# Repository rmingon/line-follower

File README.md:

## Line follower

# Line Follower Robot - ATmega2560 Based

This project is a Line Follower Robot using an ATmega2560 microcontroller. It features motor control, a reflective sensor array for line tracking, a fan controller, and voltage regulation.

### 3D views

## Features

- MCU: ATmega2560-16A
- 10x QRE1113GR reflective IR sensors
- 2x MX1508 motor drivers (H-bridge)
- MOSFET-based fan control (2N7002)
- Power via battery with 5V regulation (AMS1117)
- 6x status LEDs
- Standard AVR ISP programming header
- Custom-designed PCB

## Hardware Overview

- Sensors connect to MCU ADC pins
- Motor drivers controlled via PWM
- Fan controlled via GPIO and MOSFET
- 16 MHz crystal oscillator with 22pF caps
- Power from battery regulated to 5V

## Components

| Component      | Part             | Description                    |
|----------------|------------------|--------------------------------|
| Microcontroller| ATmega2560-16A   | Main processing unit           |
| Motor Driver   | MX1508           | H-bridge for motor control     |
| Sensor         | QRE1113GR        | IR reflective sensor           |
| Regulator      | AMS1117-5.0      | 5V linear regulator            |
| MOSFET         | 2N7002           | Fan switching control          |
| Oscillator     | 16 MHz + 22pF    | Clock for MCU                  |
| LED            | Generic Red LED  | Status indicators              |
| Fan            | 5V Fan           | Pin to floor                   |

## Key MCU Pin Mapping

| Feature         | Pin (ATmega2560) |
|----------------|------------------|
| Motor A Control| PE4, PE5         |
| Motor B Control| PG5, PL7         |
| IR Sensors     | PF0–PF9          |
| Fan Control    | PD7              |
| LEDs           | PA0–PA5          |

## PCB Layout

Two zones:
1. Sensor array in a linear top arrangement for line detection.
2. Bottom section contains MCU, drivers, power, and headers.

## Usage Steps

1. Connect a battery to `+BATT` input.
2. Upload firmware using AVR ISP (J5).
3. Place on track with visible black line.
4. Adjust PID tuning in firmware for better tracking.

## Development Tools

- KiCad for circuit & PCB design
- AVR-GCC or PlatformIO for firmware
- AVRDude for programming

## File Structure

```
/hardware
  schematic.jpeg
  pcb.png
/firmware
  main.c / main.cpp
  Makefile / platformio.ini
README.md
```

## Author

Created by Rmingon - Robotics Developer

### PCB

### SCHEMATIC

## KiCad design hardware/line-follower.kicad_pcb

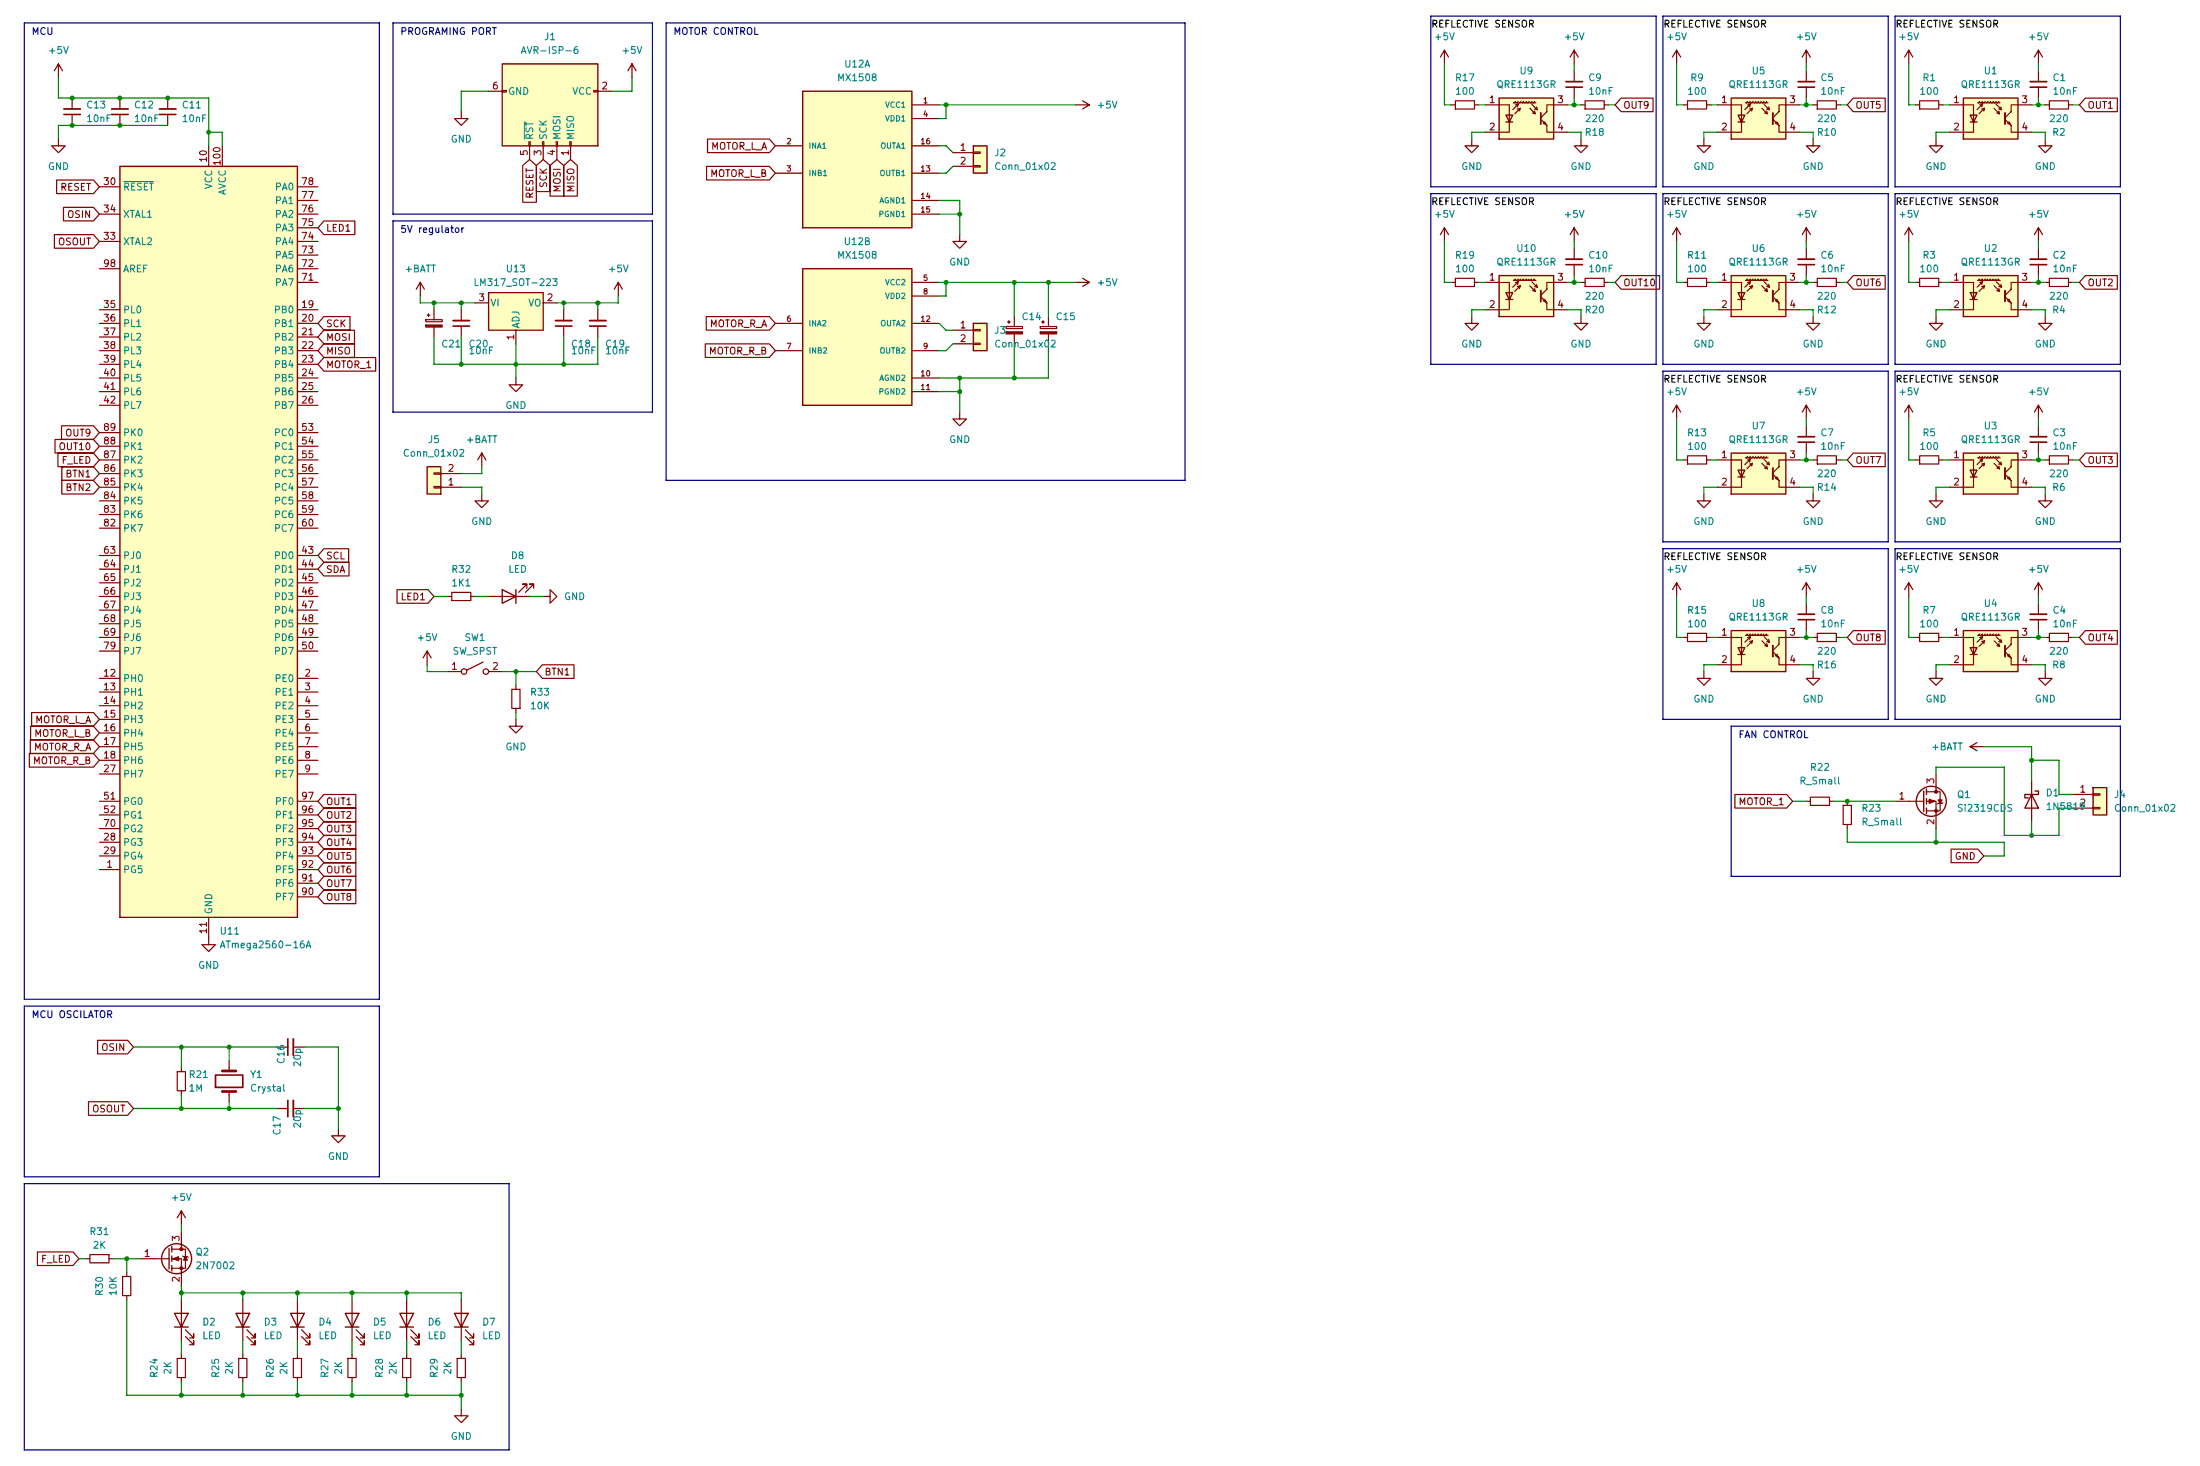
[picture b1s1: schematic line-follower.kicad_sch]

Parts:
C1, C2, C3, C4, C5, C6, C7, C8, C9, C10, C11, C12, C13, C18, C19, C20: 10nF; C_0603_1608Metric
C14, C15, C21: C_Polarized_Small; CP_Elec_6.3x4.9
C16, C17: 20p; C_0603_1608Metric
D1: 1N5819; D_DO-41_SOD81_P10.16mm_Horizontal
D2, D3, D4, D5, D6, D7, D8: LED; LED_0603_1608Metric
J1: AVR-ISP-6; PinHeader_2x03_P2.54mm_Vertical
J2, J3: Conn_01x02; PinSocket_1x02_P2.54mm_Vertical
J4: Conn_01x02; PinHeader_1x02_P2.54mm_Vertical
J5: Conn_01x02; TE_826576-2_1x02_P3.96mm_Vertical
Q1: Si2319CDS; SOT-23
Q2: 2N7002; SOT-23
R1, R3, R5, R7, R9, R11, R13, R15, R17, R19: 100; R_0603_1608Metric
R2, R4, R6, R8, R10, R12, R14, R16, R18, R20: 220; R_0603_1608Metric
R21: 1M; R_0603_1608Metric
R22, R23: R_Small; R_0603_1608Metric
R24, R25, R26, R27, R28, R29, R31: 2K; R_0603_1608Metric
R30, R33: 10K; R_0603_1608Metric
R32: 1K1; R_0603_1608Metric
SW1: SW_SPST; SW_SPST_FSMSM
U1, U2, U3, U4, U5, U6, U7, U8, U9, U10: QRE1113GR; OnSemi_CASE100CY
U11: ATmega2560-16A; TQFP-100_14x14mm_P0.5mm
U12: MX1508; SOIC-16W_5.3x10.2mm_P1.27mm
U13: LM317_SOT-223; SOT-223-3_TabPin2
Y1: Crystal; Crystal_SMD_HC49-SD

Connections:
+5V: C1.2, C2.2, C3.2, C4.2, C5.2, C6.2, C7.2, C8.2, C9.2, C10.2, C11.2, C12.2, C13.2, C14.1, C15.1, C18.2, C19.2, J1.2 (VCC), Q2.3 (D), R1.1, R3.1, R5.1, R7.1, R9.1, R11.1, R13.1, R15.1, R17.1, R19.1, SW1.1 (A), U11.10 (VCC), U11.31 (VCC), U11.61 (VCC), U11.80 (VCC), U11.100 (AVCC), U12.1 (VCC1), U12.4 (VDD1), U12.5 (VCC2), U12.8 (VDD2), U13.2 (VO)
+BATT: C20.2, C21.1, D1.1 (K), J4.1, J5.2, U13.3 (VI)
BTN1: R33.2, SW1.2 (B), U11.86 (PK3)
BTN2: U11.85 (PK4)
F_LED: R31.2, U11.87 (PK2)
GND: C11.1, C12.1, C13.1, C14.2, C15.2, C16.2, C17.2, C18.1, C19.1, C20.1, C21.2, D8.1 (K), J1.6 (GND), J5.1, Q1.2 (S), R23.2, R24.2, R25.2, R26.2, R27.2, R28.2, R29.2, R30.2, R33.1, U1.2 (K), U1.4, U2.2 (K), U2.4, U3.2 (K), U3.4, U4.2 (K), U4.4, U5.2 (K), U5.4, U6.2 (K), U6.4, U7.2 (K), U7.4, U8.2 (K), U8.4, U9.2 (K), U9.4, U10.2 (K), U10.4, U11.11 (GND), U11.32 (GND), U11.62 (GND), U11.81 (GND), U11.99 (GND), U12.10 (AGND2), U12.11 (PGND2), U12.14 (AGND1), U12.15 (PGND1), U13.1 (ADJ)
LED1: R32.1, U11.75 (PA3)
MISO: J1.1 (MISO), U11.22 (PB3)
MOSI: J1.4 (MOSI), U11.21 (PB2)
MOTOR_1: R22.1, U11.23 (PB4)
MOTOR_L_A: U11.15 (PH3), U12.2 (INA1)
MOTOR_L_B: U11.16 (PH4), U12.3 (INB1)
MOTOR_R_A: U11.17 (PH5), U12.6 (INA2)
MOTOR_R_B: U11.18 (PH6), U12.7 (INB2)
unnamed: C1.1, R2.1, U1.3
unnamed: C2.1, R4.1, U2.3
unnamed: C3.1, R6.1, U3.3
unnamed: C4.1, R8.1, U4.3
unnamed: C5.1, R10.1, U5.3
unnamed: C6.1, R12.1, U6.3
unnamed: C7.1, R14.1, U7.3
unnamed: C8.1, R16.1, U8.3
unnamed: C9.1, R18.1, U9.3
unnamed: C10.1, R20.1, U10.3
unnamed: D1.2 (A), J4.2, Q1.3 (D)
unnamed: D2.2 (A), D3.2 (A), D4.2 (A), D5.2 (A), D6.2 (A), D7.2 (A), Q2.2 (S)
unnamed: D2.1 (K), R24.1
unnamed: D3.1 (K), R25.1
unnamed: D4.1 (K), R26.1
unnamed: D5.1 (K), R27.1
unnamed: D6.1 (K), R28.1
unnamed: D7.1 (K), R29.1
unnamed: D8.2 (A), R32.2
unnamed: J2.1, U12.16 (OUTA1)
unnamed: J2.2, U12.13 (OUTB1)
unnamed: J3.1, U12.12 (OUTA2)
unnamed: J3.2, U12.9 (OUTB2)
unnamed: Q1.1 (G), R22.2, R23.1
unnamed: Q2.1 (G), R30.1, R31.1
unnamed: R1.2, U1.1 (A)
unnamed: R3.2, U2.1 (A)
unnamed: R5.2, U3.1 (A)
unnamed: R7.2, U4.1 (A)
unnamed: R9.2, U5.1 (A)
unnamed: R11.2, U6.1 (A)
unnamed: R13.2, U7.1 (A)
unnamed: R15.2, U8.1 (A)
unnamed: R17.2, U9.1 (A)
unnamed: R19.2, U10.1 (A)
OSIN: C16.1, R21.1, U11.34 (XTAL1), Y1.2
OSOUT: C17.1, R21.2, U11.33 (XTAL2), Y1.1
OUT1: R2.2, U11.97 (PF0)
OUT2: R4.2, U11.96 (PF1)
OUT3: R6.2, U11.95 (PF2)
OUT4: R8.2, U11.94 (PF3)
OUT5: R10.2, U11.93 (PF4)
OUT6: R12.2, U11.92 (PF5)
OUT7: R14.2, U11.91 (PF6)
OUT8: R16.2, U11.90 (PF7)
OUT9: R18.2, U11.89 (PK0)
OUT10: R20.2, U11.88 (PK1)
RESET: J1.5 (~RST), U11.30 (~RESET)
SCK: J1.3 (SCK), U11.20 (PB1)
SCL: U11.43 (PD0)
SDA: U11.44 (PD1)

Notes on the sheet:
MOTOR CONTROL
5V regulator
MCU OSCILATOR
PROGRAMING PORT
FAN CONTROL
MCU

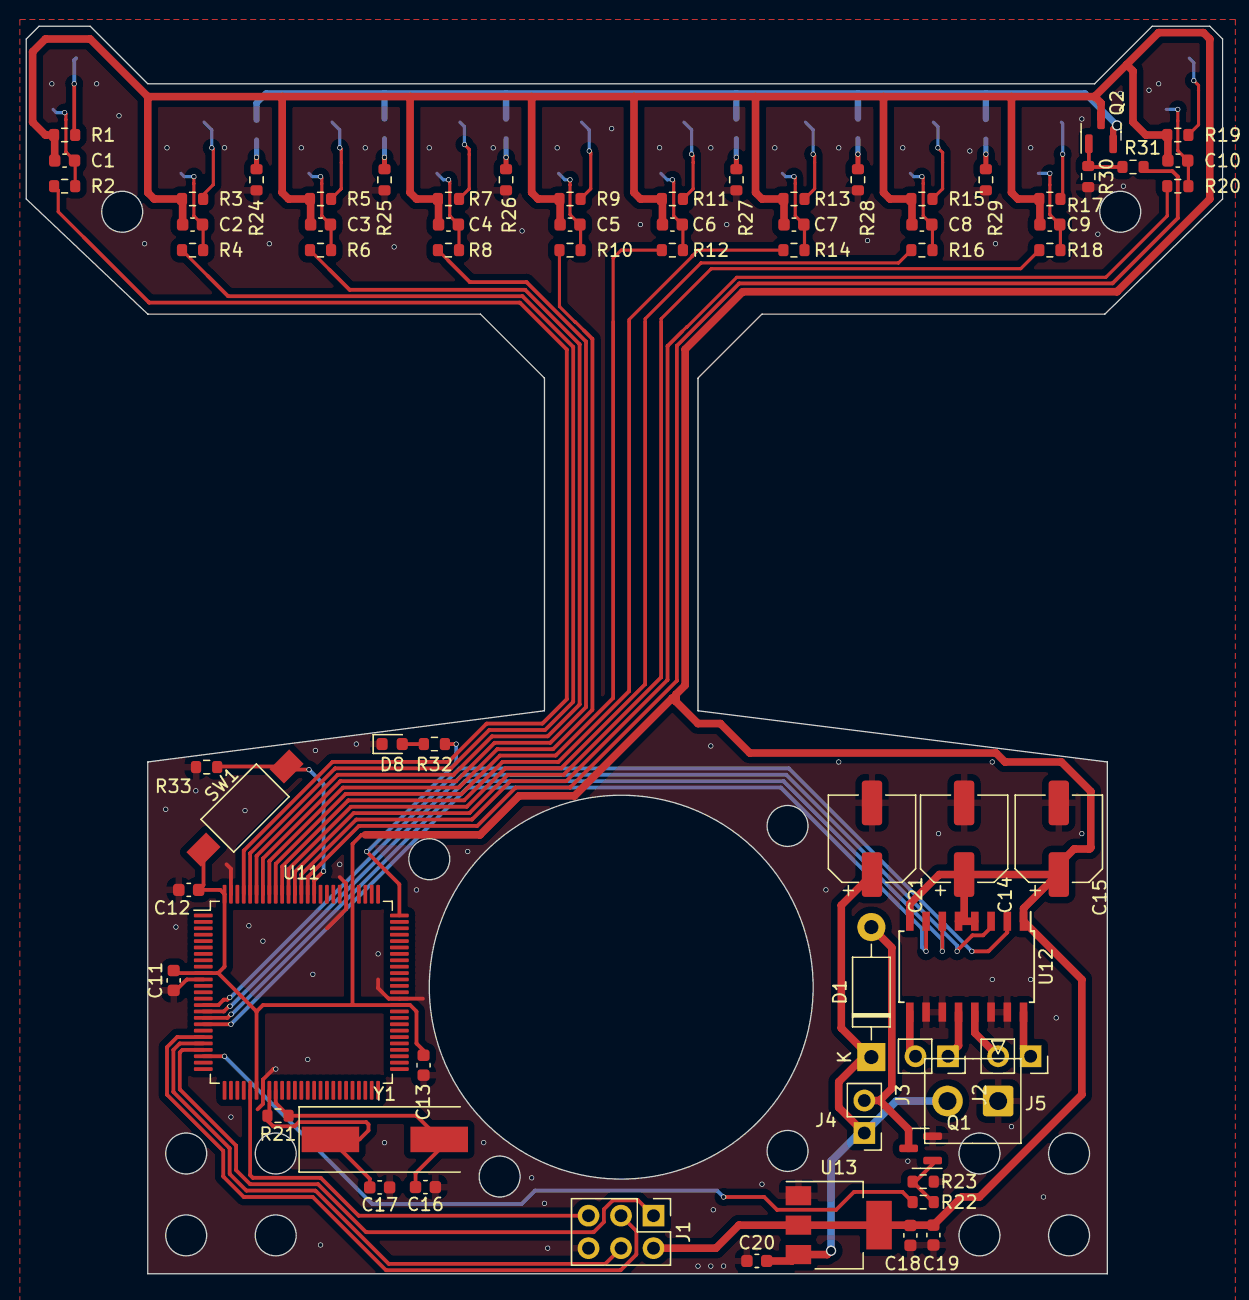
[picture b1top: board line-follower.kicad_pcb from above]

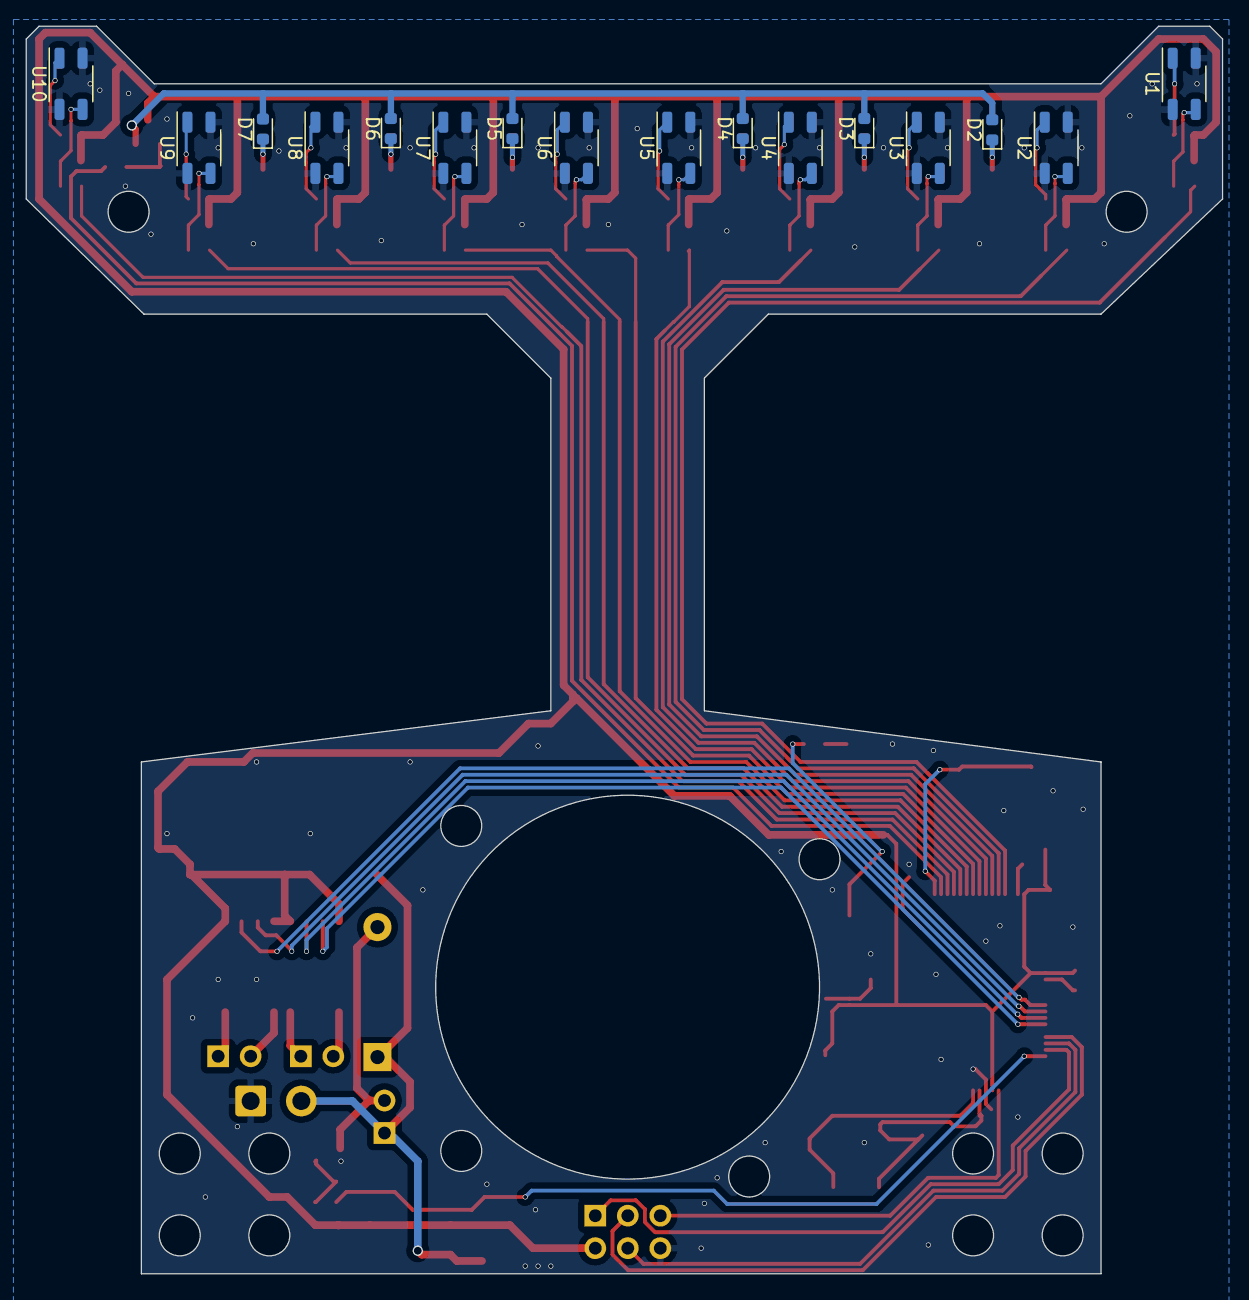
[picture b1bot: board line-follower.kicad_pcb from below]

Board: 2 copper layers, 93.5 x 97.5 mm, 84 parts (16 on the bottom side), 62 nets.

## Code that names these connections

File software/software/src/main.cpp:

#include <Arduino.h>

#define SENSITIVITY 80

// IR PIN LEFT TO RIGHT
#define IR0 PIN_PF0
#define IR1 PIN_PF1
#define IR2 PIN_PF2
#define IR3 PIN_PF3
#define IR4 PIN_PF4
#define IR5 PIN_PF5
#define IR6 PIN_PF6
#define IR7 PIN_PF7
#define IR8 PIN_PK0
#define IR9 PIN_PK1

#define FAN PIN_PB4

// MX1508
#define MOTOR_L_A PIN_PH3
#define MOTOR_L_B PIN_PH4
#define MOTOR_R_A PIN_PH5
#define MOTOR_R_B PIN_PH6

// LEDS BOTTOM
#define LEDS PIN_PK2

#define BUTTON PIN_PK3

bool run = false;

void setup() {
  pinMode(PIN_PA3, OUTPUT);
  pinMode(BUTTON, INPUT);
  pinMode(FAN, OUTPUT);

  pinMode(LEDS, OUTPUT);
  
  pinMode(MOTOR_L_A, OUTPUT);
  pinMode(MOTOR_L_B, OUTPUT);
  pinMode(MOTOR_R_A, OUTPUT);
  pinMode(MOTOR_R_B, OUTPUT);
  analogWrite(MOTOR_L_A, 0);
  analogWrite(MOTOR_L_B, 0);
  analogWrite(MOTOR_R_A, 0);
  analogWrite(MOTOR_R_B, 0);
  
  pinMode(IR3, INPUT);
  pinMode(IR4, INPUT);
  pinMode(IR5, INPUT);
  pinMode(IR6, INPUT);
}

void loop() {
  if (digitalRead(BUTTON)) {
    delay(300);
    run = !run;
  }
  if (run) {
    // analogWrite(FAN, 10);
    
    digitalWrite(LEDS, HIGH);
    int ir4 = analogRead(IR4);
    if (ir4 > SENSITIVITY) {
      analogWrite(MOTOR_L_B, 60);
    } else {
      analogWrite(MOTOR_L_B, 0);
    }
    int ir5 = analogRead(IR5);
    if (ir5 > SENSITIVITY) {
      analogWrite(MOTOR_R_A, 60);
    } else {
      analogWrite(MOTOR_R_A, 0);
    }

  } else {
    
    digitalWrite(LEDS, LOW);
    analogWrite(FAN, 0);
    
    analogWrite(MOTOR_L_B, 0);
      
    analogWrite(MOTOR_R_A, 0);
  }

}

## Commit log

2024-06-29 add captors array
2024-06-29 array wiring
2024-06-30 add mcu
2024-06-30 add hole for fan
2024-06-30 add regulator
2024-06-30 add views
2024-06-30 add battery connector
2024-06-30 add pictures
2024-06-30 update syntax
2024-06-30 add led + switch
2024-07-01 update cam path
2024-07-16 update active layer
2024-07-16 first commit code
2024-07-16 add video
2024-07-24 add motor test
2024-07-26 update version
2024-07-30 test fan
2024-08-12 change pwm
2024-08-13 add 3d fan
2024-08-13 follow minimal
2025-01-27 Update README.md
    add a video link
